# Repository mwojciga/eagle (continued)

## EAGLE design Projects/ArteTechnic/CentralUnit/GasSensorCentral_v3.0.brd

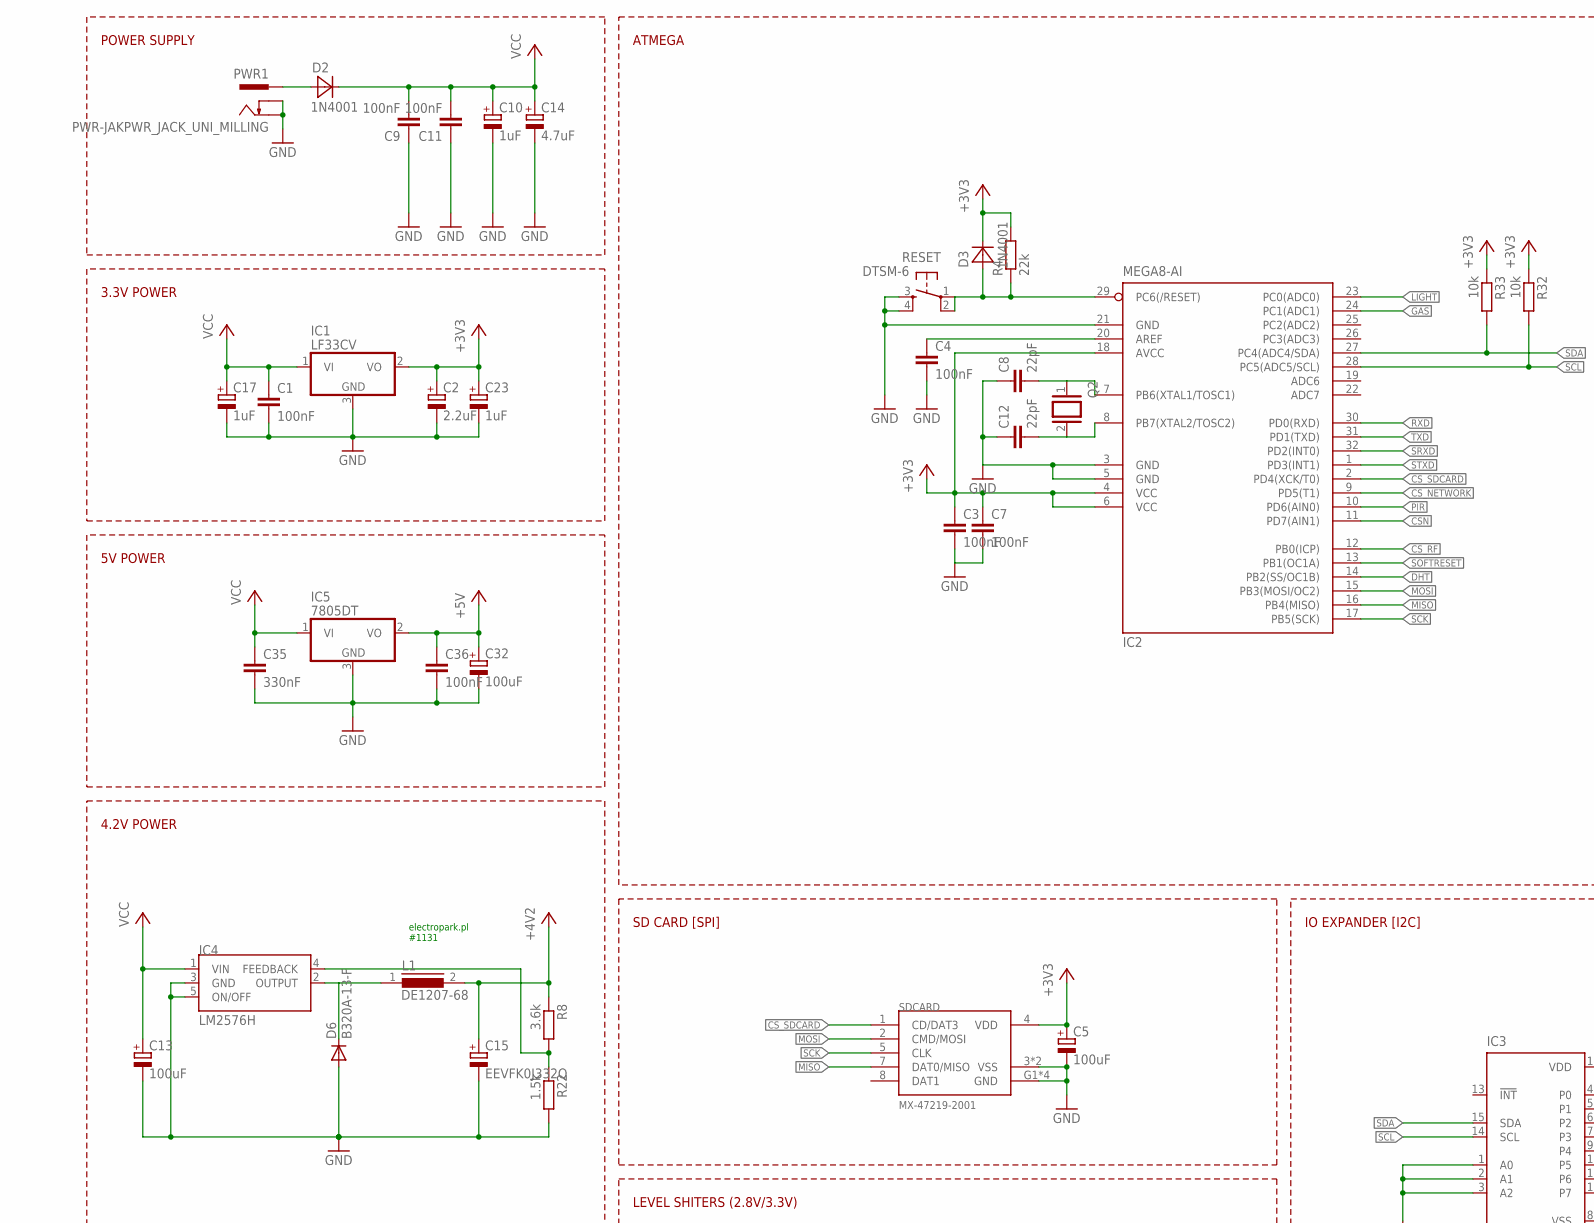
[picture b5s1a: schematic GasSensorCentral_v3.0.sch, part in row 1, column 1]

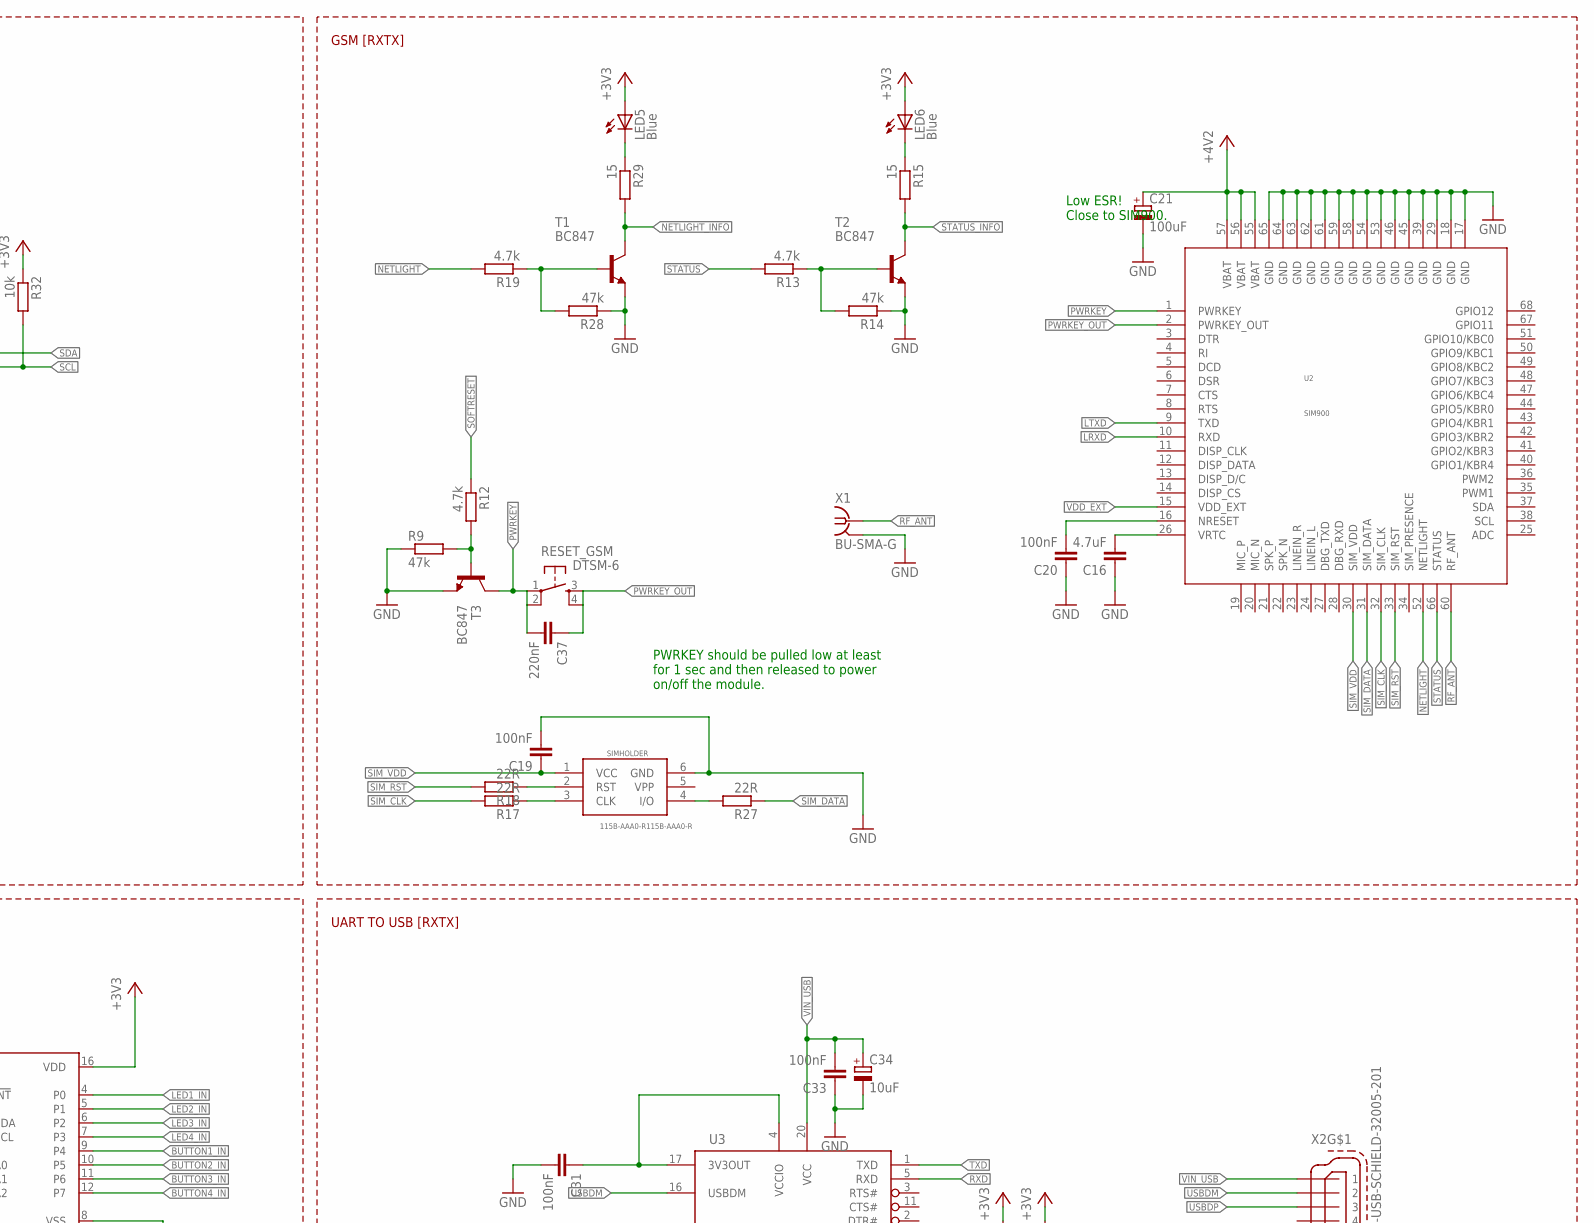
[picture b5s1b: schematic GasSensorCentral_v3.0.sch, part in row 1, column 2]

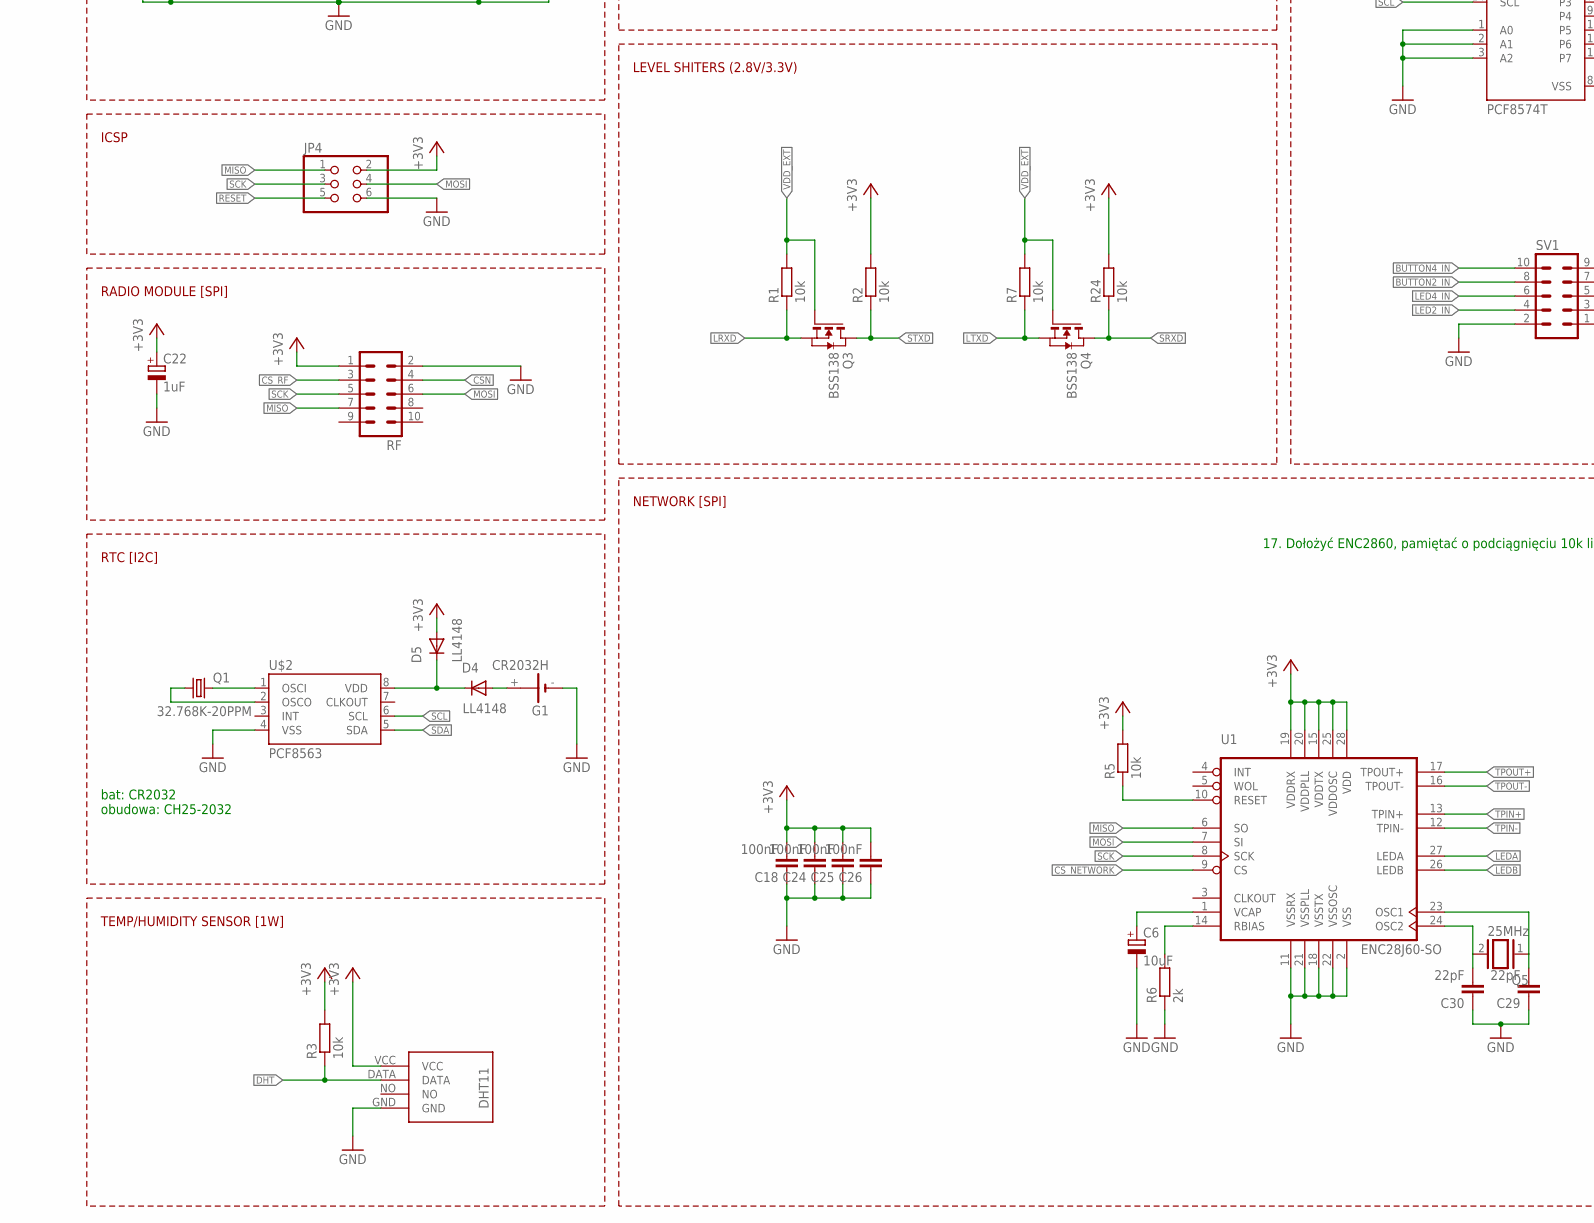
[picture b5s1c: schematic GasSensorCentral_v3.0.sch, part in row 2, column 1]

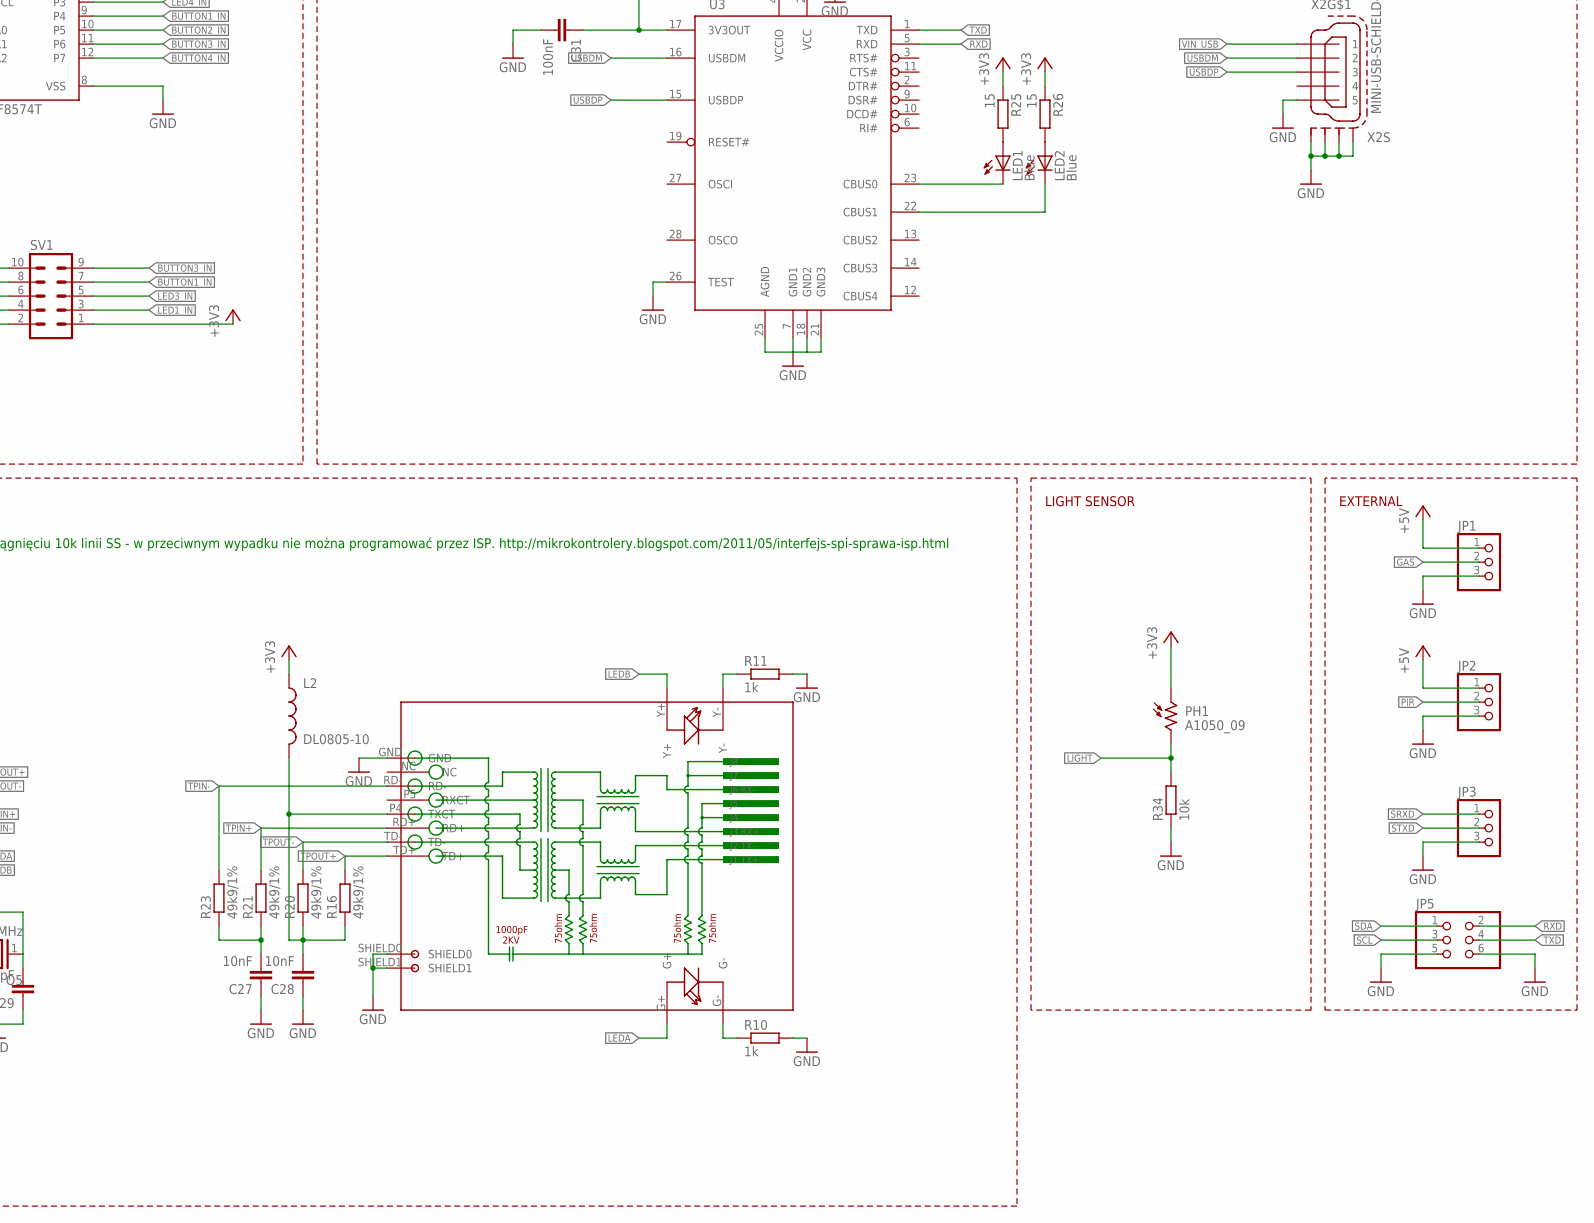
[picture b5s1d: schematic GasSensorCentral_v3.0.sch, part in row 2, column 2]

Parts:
C1, C3, C4, C7, C9, C11, C18, C19, C20, C24, C25, C26, C31, C33, C36: 100nF; C0805
C2: 2.2uF; PANASONIC_B
C5, C13, C21, C32: 100uF; PANASONIC_B
C6, C34: 10uF; PANASONIC_B
C8, C12, C29, C30: 22pF; C0805
C10, C17, C22, C23: 1uF; PANASONIC_B
C14: 4.7uF; PANASONIC_B
C15: EEVFK0J332Q; 153CLV-1212
C16: 4.7uF; C0805
C27, C28: 10nF; C0805
C35: 330nF; C0805
C37: 220nF; C0805
D2, D3: 1N4001; SMA
D4, D5: LL4148; SOD80C
D6: B320A-13-F; DO214AC
G1: CR2032H
IC1: LF33CV; TO252
IC2: MEGA8-AI; TQFP32-08
IC3: PCF8574T; SO16W
IC4: LM2576H; TO220-52
IC5: 7805DT; TO252
JP1, JP2, JP3: PINHD-1X3; 1X03
JP4, JP5: PINHD-2X3; 2X03
L1: DE1207-68; DE1207
L2: DL0805-10; 0805
LED1, LED2, LED5, LED6: Blue; SML0805
PH1: A1050_09; T0-46-A10XX
PWR1: PWR-JAKPWR_JACK_UNI_MILLING; PWR_JACK_UNI_MILLING
Q1: 32.768K-20PPM; TC26V
Q2: XTAL/S; QS
Q3, Q4: BSS138; SOT-23
Q5: 25MHz; QS
R1, R2, R3, R5, R7, R24, R32, R33, R34: 10k; R0805
R4: 22k; R0805
R6: 2k; R0805
R8: 3.6k; R0805
R9, R14, R28: 47k; R0805
R10, R11: 1k; R0805
R12, R13, R19: 4.7k; R0805
R15, R25, R26, R29: 15; R0805
R16, R20, R21, R23: 49k9/1%; R0805
R17, R18, R27: 22R; R0805
R22: 1.5k; R0805
RESET: DTSM-6
RESET_GSM: DTSM-6
RF: ML10
RJ1: HR911105A
SDCARD: MX-47219-2001
SIMHOLDER: 115B-AAA0-R115B-AAA0-R; 115B-AAA0-R
SV1: ML10
T1, T2, T3: BC847; SOT23
U1: ENC28J60-SO; SO28W
U2: SIM900
U3: FT232RL; SSOP28DB
U$2: PCF8563; SO08
U$3: DHT11-PION.
X1: BU-SMA-G
X2: MINI-USB-SCHIELD-32005-201; 32005-201

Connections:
+3V3: C2.+, C3.1, C5.+, C7.1, C18.2, C22.+, C23.+, C24.2, C25.2, C26.2, D3.C, D5.A, IC1.2 (VO), IC2.4 (VCC), IC2.6 (VCC), IC2.18 (AVCC), IC3.16 (VDD), JP4.2, L2.1, LED5.A, LED6.A, PH1.1, R2.2, R3.2, R4.2, R5.2, R24.2, R25.1, R26.1, R32.1, R33.1, RF.1, SDCARD.4 (VDD), SV1.1, U1.15 (VDDTX), U1.19 (VDDRX), U1.20 (VDDPLL), U1.25 (VDDOSC), U1.28 (VDD), U$3.VCC
+4V2: C15.+, C21.+, L1.2, R8.1, U2.55 (VBAT), U2.56 (VBAT), U2.57 (VBAT)
+5V: C32.+, C36.1, IC5.2 (VO), JP1.1, JP2.1
BUTTON1_IN: IC3.9 (P4), SV1.7
BUTTON2_IN: IC3.10 (P5), SV1.8
BUTTON3_IN: IC3.11 (P6), SV1.9
BUTTON4_IN: IC3.12 (P7), SV1.10
CSN: IC2.11 (PD7(AIN1)), RF.4
CS_NETWORK: IC2.9 (PD5(T1)), U1.9 (CS)
CS_RF: IC2.12 (PB0(ICP)), RF.3
CS_SDCARD: IC2.2 (PD4(XCK/T0)), SDCARD.1 (CD/DAT3)
DHT: IC2.14 (PB2(SS/OC1B)), R3.1, U$3.DATA
GAS: IC2.24 (PC1(ADC1)), JP1.2
GND: C1.2, C2.-, C3.2, C4.2, C5.-, C6.-, C7.2, C8.1, C9.1, C10.-, C11.1, C12.1, C13.-, C14.-, C15.-, C16.1, C17.-, C18.1, C19.2, C20.1, C21.-, C22.-, C23.-, C24.1, C25.1, C26.1, C27.1, C28.1, C29.1, C30.1, C31.2, C32.-, C33.1, C34.-, C35.2, C36.2, G1.-, IC1.3 (GND), IC2.3 (GND), IC2.5 (GND), IC2.21 (GND), IC3.1 (A0), IC3.2 (A1), IC3.3 (A2), IC3.8 (VSS), IC4.3 (GND), IC4.5 (ON/OFF), IC5.3 (GND), JP1.3, JP2.3, JP3.3, JP4.6, JP5.5, JP5.6, PWR1.-, PWR1.-1 (-), PWR1.-2 (-), PWR1.-3 (-), PWR1.-4 (-), PWR1.-5 (-), PWR1.-6 (-), PWR1.--, PWR1.--1 (--), PWR1.--2 (--), PWR1.--3 (--), PWR1.--4 (--), PWR1.--5 (--), PWR1.--6 (--), R6.1, R9.1, R10.2, R11.2, R14.1, R22.2, R28.1, R34.1, RESET.3, RESET.4, RF.2, RJ1.GND, RJ1.SHIELD0, RJ1.SHIELD1, SDCARD.3 (VSS), SDCARD.6 (VSS), SDCARD.G1 (GND), SDCARD.G2 (GND), SDCARD.G3 (GND), SDCARD.G4 (GND), SIMHOLDER.6 (GND), SV1.2, T1.2 (E), T2.2 (E), T3.2 (E), U1.2 (VSS), U1.11 (VSSRX), U1.18 (VSSTX), U1.21 (VSSPLL), U1.22 (VSSOSC), U2.17 (GND), U2.18 (GND), U2.29 (GND), U2.39 (GND), U2.45 (GND), U2.46 (GND), U2.53 (GND), U2.54 (GND), U2.58 (GND), U2.59 (GND), U2.61 (GND), U2.62 (GND), U2.63 (GND), U2.64 (GND), U2.65 (GND), U3.7 (GND1), U3.18 (GND2), U3.21 (GND3), U3.25 (AGND), U3.26 (TEST), U$2.4 (VSS), U$3.GND, X1.2, X1.3 (2), X1.4 (2), X1.5 (2), X2.5, X2.M1 (S1), X2.M2 (S2), X2.M3 (S3), X2.M4 (S4)
LED1_IN: IC3.4 (P0), SV1.3
LED2_IN: IC3.5 (P1), SV1.4
LED3_IN: IC3.6 (P2), SV1.5
LED4_IN: IC3.7 (P3), SV1.6
LEDA: RJ1.G+, U1.27 (LEDA)
LEDB: RJ1.Y+, U1.26 (LEDB)
LIGHT: IC2.23 (PC0(ADC0)), PH1.2, R34.2
LRXD: Q3.2 (S), R1.1, U2.10 (RXD)
LTXD: Q4.2 (S), R7.1, U2.9 (TXD)
MISO: IC2.16 (PB4(MISO)), JP4.1, RF.7, SDCARD.7 (DAT0/MISO), U1.6 (SO)
MOSI: IC2.15 (PB3(MOSI/OC2)), JP4.4, RF.6, SDCARD.2 (CMD/MOSI), U1.7 (SI)
unnamed: C4.1, IC2.20 (AREF)
unnamed: Q1.1, U$2.2 (OSCO)
unnamed: IC4.4 (FEEDBACK), R8.2, R22.1
unnamed: D2.A, PWR1.+, PWR1.+1 (+), PWR1.+2 (+), PWR1.+3 (+), PWR1.+4 (+), PWR1.+5 (+), PWR1.+6 (+)
unnamed: D4.C, D5.C, U$2.8 (VDD)
unnamed: R27.2, SIMHOLDER.4 (I/O)
unnamed: LED5.C, R29.1
unnamed: Q1.2, U$2.1 (OSCI)
unnamed: R13.1, R14.2, T2.1 (B)
unnamed: LED6.C, R15.1
unnamed: D6.C, IC4.2 (OUTPUT), L1.1
unnamed: C20.2, U2.16 (NRESET)
unnamed: R9.2, R12.2, T3.1 (B)
unnamed: R19.1, R28.2, T1.1 (B)
unnamed: D4.A, G1.+
unnamed: C16.2, U2.26 (VRTC)
unnamed: R5.1, U1.10 (RESET)
unnamed: C6.+, U1.1 (VCAP)
unnamed: R6.2, U1.14 (RBIAS)
unnamed: R11.1, RJ1.Y-
unnamed: R10.1, RJ1.G-
unnamed: C29.2, Q5.1, U1.23 (OSC1)
unnamed: R18.1, SIMHOLDER.2 (RST)
unnamed: R17.1, SIMHOLDER.3 (CLK)
unnamed: C30.2, Q5.2, U1.24 (OSC2)
unnamed: LED1.C, U3.23 (CBUS0)
unnamed: LED2.C, U3.22 (CBUS1)
unnamed: C8.2, IC2.7 (PB6(XTAL1/TOSC1)), Q2.1
unnamed: C27.2, R21.1, R23.1
unnamed: C28.2, L2.2, R16.1, R20.1, RJ1.P4 (TXCT)
unnamed: LED1.A, R25.2
unnamed: LED2.A, R26.2
unnamed: C12.2, IC2.8 (PB7(XTAL2/TOSC2)), Q2.2
unnamed: C31.1, U3.4 (VCCIO), U3.17 (3V3OUT)
NETLIGHT: R19.2, U2.52 (NETLIGHT)
NETLIGHT_INFO: R29.2, T1.3 (C)
PIR: IC2.10 (PD6(AIN0)), JP2.2
PWRKEY: C37.2, RESET_GSM.1, RESET_GSM.2, T3.3 (C), U2.1 (PWRKEY)
PWRKEY_OUT: C37.1, RESET_GSM.3, RESET_GSM.4, U2.2 (PWRKEY_OUT)
RESET: D3.A, IC2.29 (PC6(/RESET)), JP4.5, R4.1, RESET.1, RESET.2
RF_ANT: U2.60 (RF_ANT), X1.1
RXD: IC2.30 (PD0(RXD)), JP5.2, U3.5 (RXD)
SCK: IC2.17 (PB5(SCK)), JP4.3, RF.5, SDCARD.5 (CLK), U1.8 (SCK)
SCL: IC2.28 (PC5(ADC5/SCL)), IC3.14 (SCL), JP5.3, R32.2, U$2.6 (SCL)
SDA: IC2.27 (PC4(ADC4/SDA)), IC3.15 (SDA), JP5.1, R33.2, U$2.5 (SDA)
SIM_CLK: R17.2, U2.32 (SIM_CLK)
SIM_DATA: R27.1, U2.31 (SIM_DATA)
SIM_RST: R18.2, U2.33 (SIM_RST)
SIM_VDD: C19.1, SIMHOLDER.1 (VCC), U2.30 (SIM_VDD)
SOFTRESET: IC2.13 (PB1(OC1A)), R12.1
SRXD: IC2.32 (PD2(INT0)), JP3.1, Q4.1 (D), R24.1
STATUS: R13.2, U2.66 (STATUS)
STATUS_INFO: R15.2, T2.3 (C)
STXD: IC2.1 (PD3(INT1)), JP3.2, Q3.1 (D), R2.1
TPIN+: R21.2, RJ1.RD+, U1.13 (TPIN+)
TPIN-: R23.2, RJ1.RD-, U1.12 (TPIN-)
TPOUT+: R16.2, RJ1.TD+, U1.17 (TPOUT+)
TPOUT-: R20.2, RJ1.TD-, U1.16 (TPOUT-)
TXD: IC2.31 (PD1(TXD)), JP5.4, U3.1 (TXD)
USBDM: U3.16 (USBDM), X2.2
USBDP: U3.15 (USBDP), X2.3
VCC: C1.1, C9.2, C10.+, C11.2, C13.+, C14.+, C17.+, C35.1, D2.C, IC1.1 (VI), IC4.1 (VIN), IC5.1 (VI)
VDD_EXT: Q3.3 (G), Q4.3 (G), R1.2, R7.2, U2.15 (VDD_EXT)
VIN_USB: C33.2, C34.+, U3.20 (VCC), X2.1

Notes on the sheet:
PWRKEY should be pulled low at least for 1 sec and then released to power on/off the module.
Low ESR! Close to SIM900.
bat: CR2032 obudowa: CH25-2032
POWER SUPPLY
3.3V POWER
ICSP
4.2V POWER
RADIO MODULE [SPI]
LEVEL SHITERS (2.8V/3.3V)
ATMEGA
SD CARD [SPI]
RTC [I2C]
GSM [RXTX]
NETWORK [SPI]
17. Dołożyć ENC2860, pamiętać o podciągnięciu 10k linii SS - w przeciwnym wypadku nie można programować przez ISP. http://mikrokontrolery.blogspot.com/2011/05/interfejs-spi-sprawa-isp.html
IO EXPANDER [I2C]
TEMP/HUMIDITY SENSOR [1W]
electropark.pl #1131
UART TO USB [RXTX]
LIGHT SENSOR
EXTERNAL
5V POWER

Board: 2 copper layers, 115 parts (5 on the bottom side), 89 nets, no tracks yet.

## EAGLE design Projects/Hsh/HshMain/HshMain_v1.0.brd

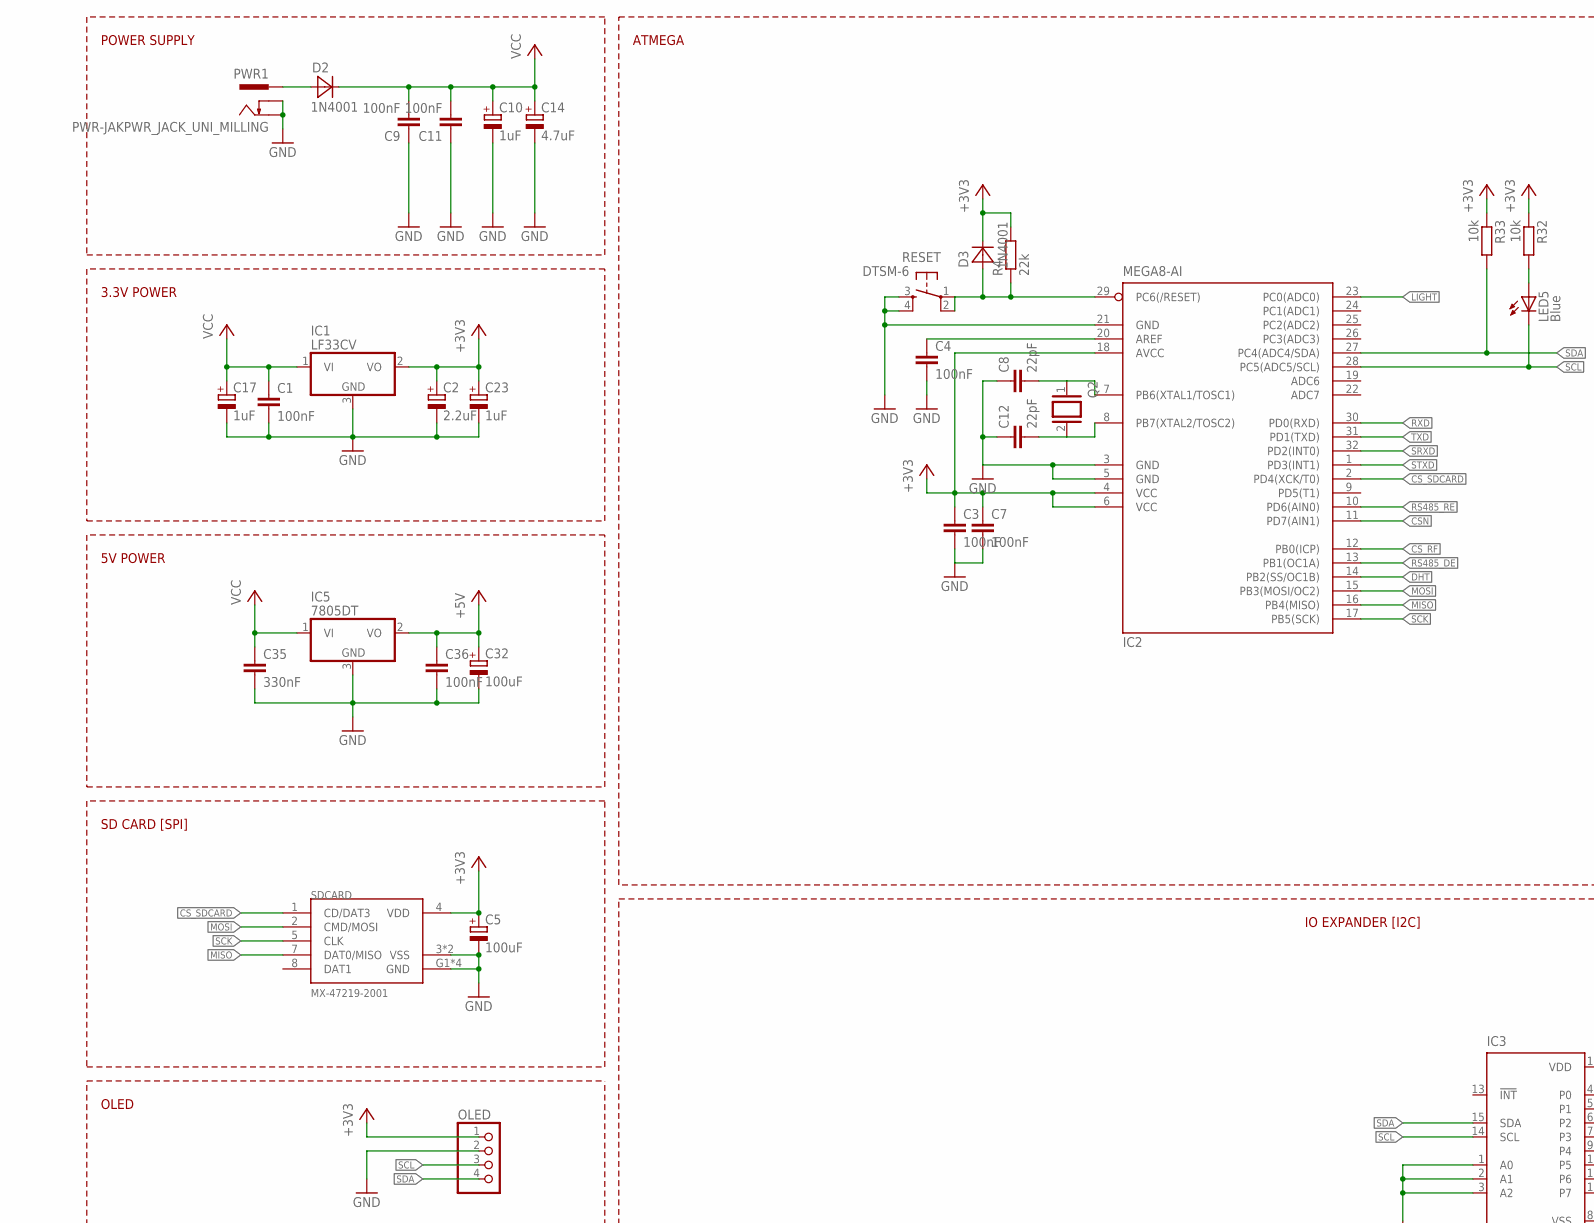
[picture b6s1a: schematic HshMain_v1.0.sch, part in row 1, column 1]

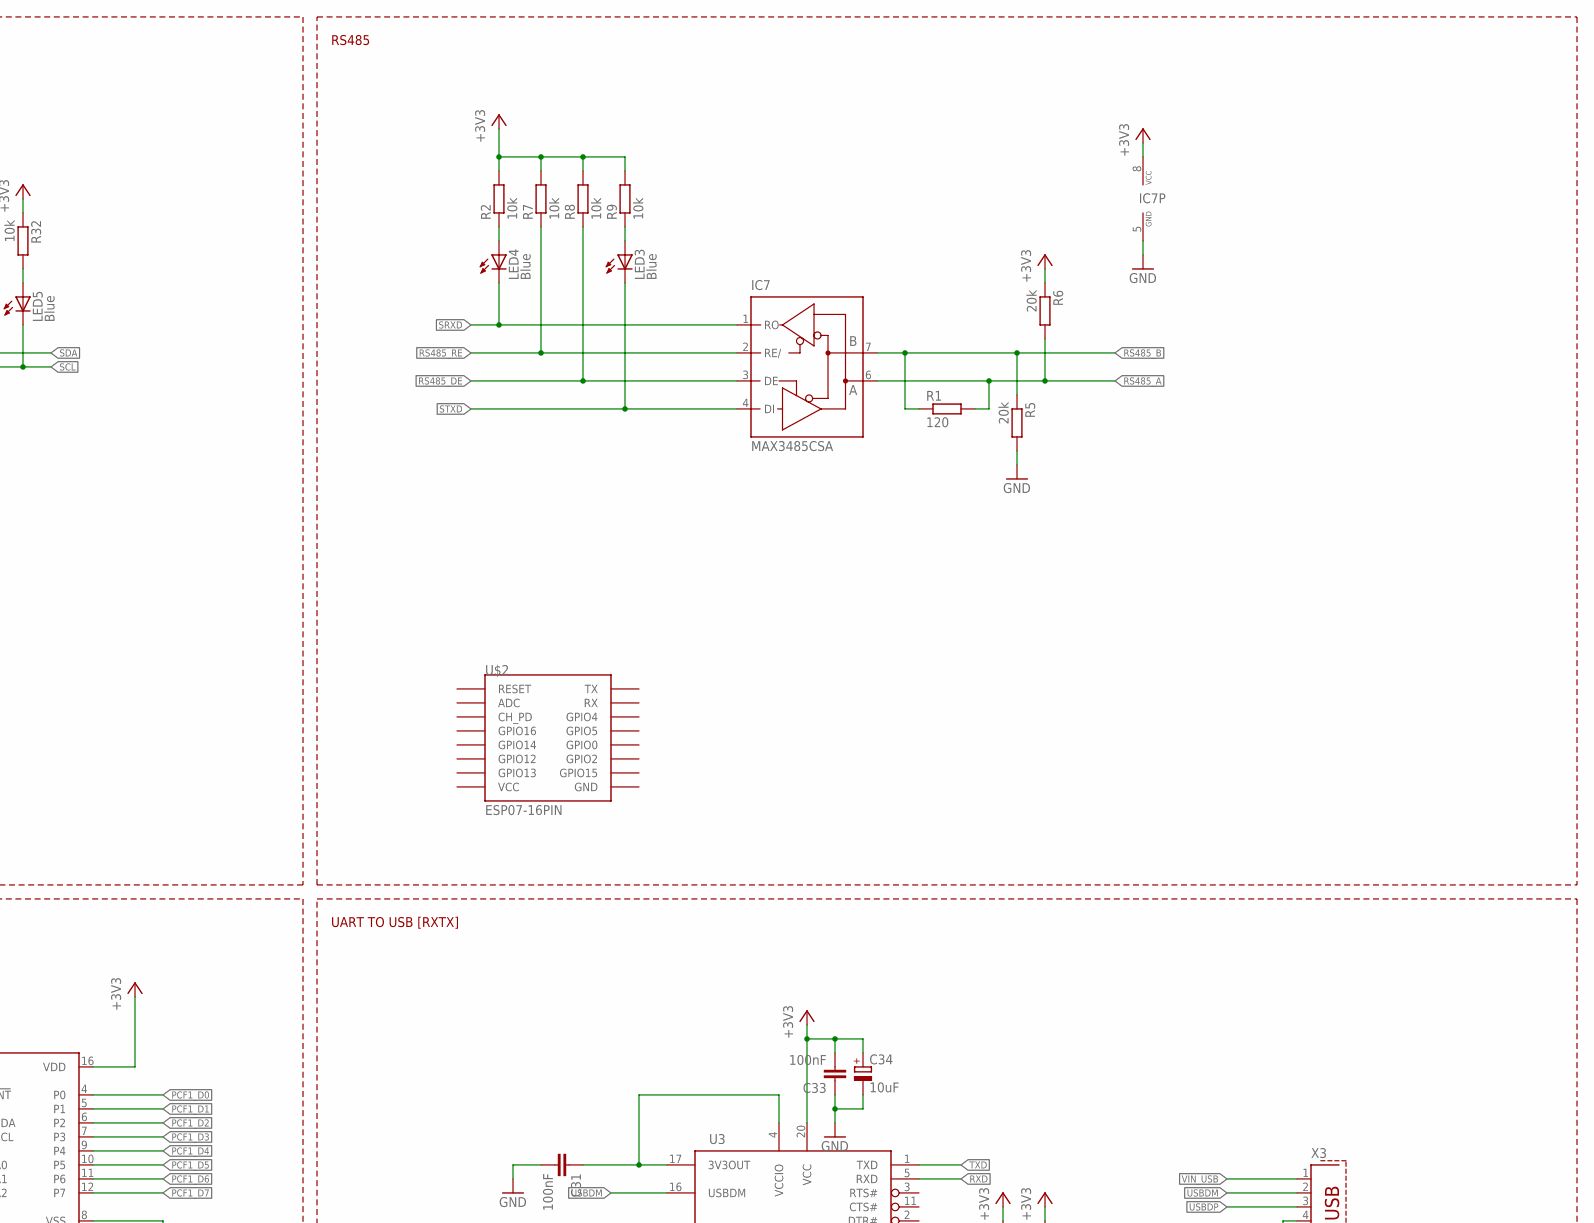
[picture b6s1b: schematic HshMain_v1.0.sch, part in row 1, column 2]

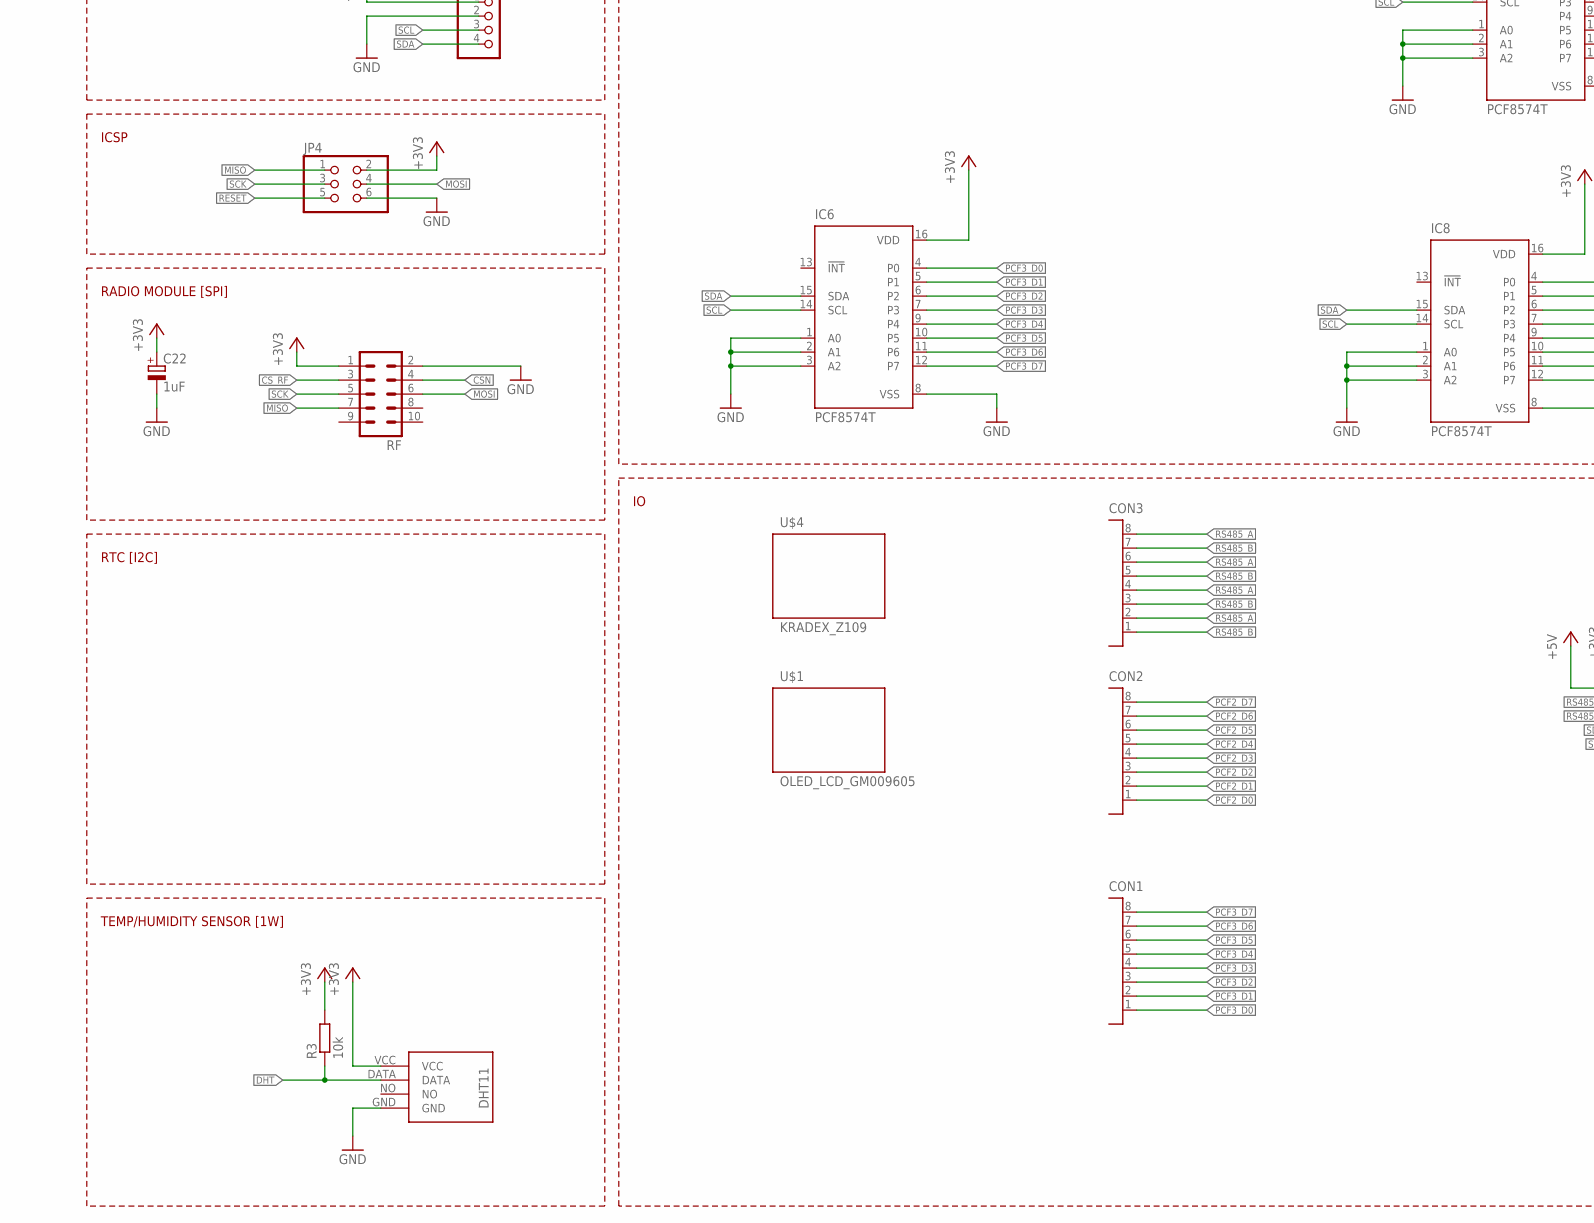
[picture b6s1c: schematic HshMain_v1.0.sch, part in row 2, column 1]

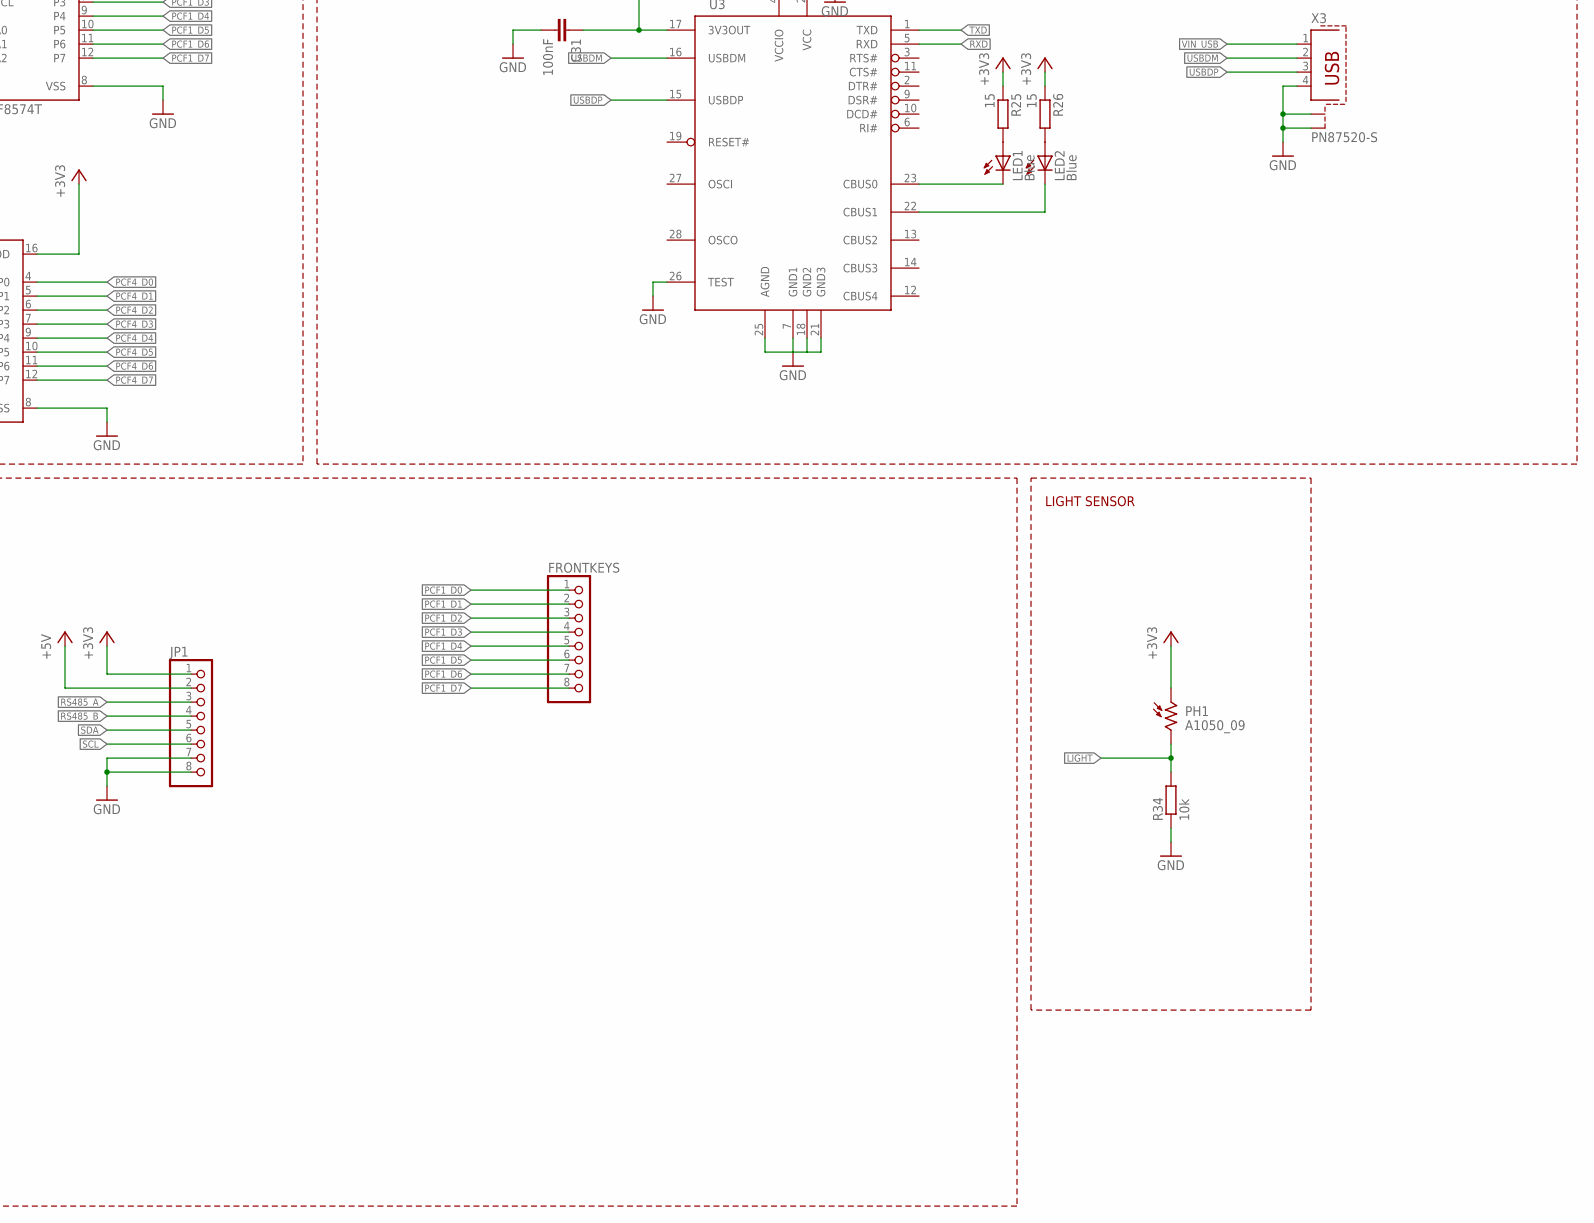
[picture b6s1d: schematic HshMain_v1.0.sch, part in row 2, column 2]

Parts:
C1, C3, C4, C7, C9, C11, C31, C33, C36: 100nF; C0805
C2: 2.2uF; PANASONIC_B
C5, C32: 100uF; PANASONIC_D
C8, C12: 22pF; C0805
C10, C17, C22, C23: 1uF; PANASONIC_B
C14: 4.7uF; PANASONIC_B
C34: 10uF; PANASONIC_B
C35: 330nF; C0805
CON1, CON2, CON3: 15EDGRC-3.81-8P
D2, D3: 1N4001; SMA
FRONTKEYS: PINHD-1X8/90; 1X08/90
IC1: LF33CV; TO252
IC2: MEGA8-AI; TQFP32-08
IC3, IC6, IC8: PCF8574T; SO16W
IC5: 7805DT; TO252
IC7: MAX3485CSA; SO08
JP1: PINHD-1X8/90; 1X08/90
JP4: PINHD-2X3; 2X03
LED1, LED2, LED3, LED4, LED5: Blue; SML0805
OLED: PINHD-1X4; 1X04
PH1: A1050_09; T0-46-A10XX
PWR1: PWR-JAKPWR_JACK_UNI_MILLING; PWR_JACK_UNI_MILLING
Q2: XTAL/S; QS
R1: 120; R0805
R2, R3, R7, R8, R9, R32, R33, R34: 10k; R0805
R4: 22k; R0805
R5, R6: 20k; R0805
R25, R26: 15; R0805
RESET: DTSM-6
RF: ML10
SDCARD: MX-47219-2001
U3: FT232RL; SSOP28DB
U$1: OLED_LCD_GM009605
U$2: ESP07-16PIN
U$3: DHT11-PION.
U$4: KRADEX_Z109
X3: PN87520-S

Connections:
+3V3: C2.+, C3.1, C5.+, C7.1, C22.+, C23.+, C33.2, C34.+, D3.C, IC1.2 (VO), IC2.4 (VCC), IC2.6 (VCC), IC2.18 (AVCC), IC3.16 (VDD), IC6.16 (VDD), IC7.8 (VCC), IC8.16 (VDD), JP1.1, JP4.2, OLED.1, PH1.1, R2.2, R3.2, R4.2, R6.1, R7.2, R8.2, R9.2, R25.1, R26.1, R32.1, R33.1, RF.1, SDCARD.4 (VDD), U3.20 (VCC), U$3.VCC
+5V: C32.+, C36.1, IC5.2 (VO), JP1.2
CSN: IC2.11 (PD7(AIN1)), RF.4
CS_RF: IC2.12 (PB0(ICP)), RF.3
CS_SDCARD: IC2.2 (PD4(XCK/T0)), SDCARD.1 (CD/DAT3)
DHT: IC2.14 (PB2(SS/OC1B)), R3.1, U$3.DATA
GND: C1.2, C2.-, C3.2, C4.2, C5.-, C7.2, C8.1, C9.1, C10.-, C11.1, C12.1, C14.-, C17.-, C22.-, C23.-, C31.2, C32.-, C33.1, C34.-, C35.2, C36.2, IC1.3 (GND), IC2.3 (GND), IC2.5 (GND), IC2.21 (GND), IC3.1 (A0), IC3.2 (A1), IC3.3 (A2), IC3.8 (VSS), IC5.3 (GND), IC6.1 (A0), IC6.2 (A1), IC6.3 (A2), IC6.8 (VSS), IC7.5 (GND), IC8.1 (A0), IC8.2 (A1), IC8.3 (A2), IC8.8 (VSS), JP1.7, JP1.8, JP4.6, OLED.2, PWR1.-, PWR1.-1 (-), PWR1.-2 (-), PWR1.-3 (-), PWR1.-4 (-), PWR1.-5 (-), PWR1.-6 (-), PWR1.-7 (-), PWR1.-8 (-), PWR1.--, PWR1.--1 (--), PWR1.--2 (--), PWR1.--3 (--), PWR1.--4 (--), PWR1.--5 (--), PWR1.--6 (--), PWR1.--7 (--), PWR1.--8 (--), R5.2, R34.1, RESET.3, RESET.4, RF.2, SDCARD.3 (VSS), SDCARD.6 (VSS), SDCARD.G1 (GND), SDCARD.G2 (GND), SDCARD.G3 (GND), SDCARD.G4 (GND), U3.7 (GND1), U3.18 (GND2), U3.21 (GND3), U3.25 (AGND), U3.26 (TEST), U$3.GND, X3.4, X3.S1, X3.S2
LIGHT: IC2.23 (PC0(ADC0)), PH1.2, R34.2
MISO: IC2.16 (PB4(MISO)), JP4.1, RF.7, SDCARD.7 (DAT0/MISO)
MOSI: IC2.15 (PB3(MOSI/OC2)), JP4.4, RF.6, SDCARD.2 (CMD/MOSI)
unnamed: C4.1, IC2.20 (AREF)
unnamed: LED4.A, R2.1
unnamed: LED3.A, R9.1
unnamed: D2.A, PWR1.+, PWR1.+1 (+), PWR1.+2 (+), PWR1.+3 (+), PWR1.+4 (+), PWR1.+5 (+), PWR1.+6 (+), PWR1.+7 (+), PWR1.+8 (+)
unnamed: LED5.A, R32.2
unnamed: LED1.C, U3.23 (CBUS0)
unnamed: LED2.C, U3.22 (CBUS1)
unnamed: C8.2, IC2.7 (PB6(XTAL1/TOSC1)), Q2.1
unnamed: LED1.A, R25.2
unnamed: LED2.A, R26.2
unnamed: C12.2, IC2.8 (PB7(XTAL2/TOSC2)), Q2.2
unnamed: C31.1, U3.4 (VCCIO), U3.17 (3V3OUT)
PCF1_D0: FRONTKEYS.1, IC3.4 (P0)
PCF1_D1: FRONTKEYS.2, IC3.5 (P1)
PCF1_D2: FRONTKEYS.3, IC3.6 (P2)
PCF1_D3: FRONTKEYS.4, IC3.7 (P3)
PCF1_D4: FRONTKEYS.5, IC3.9 (P4)
PCF1_D5: FRONTKEYS.6, IC3.10 (P5)
PCF1_D6: FRONTKEYS.7, IC3.11 (P6)
PCF1_D7: FRONTKEYS.8, IC3.12 (P7)
PCF2_D0: CON2.1
PCF2_D1: CON2.2
PCF2_D2: CON2.3
PCF2_D3: CON2.4
PCF2_D4: CON2.5
PCF2_D5: CON2.6
PCF2_D6: CON2.7
PCF2_D7: CON2.8
PCF3_D0: CON1.1, IC6.4 (P0)
PCF3_D1: CON1.2, IC6.5 (P1)
PCF3_D2: CON1.3, IC6.6 (P2)
PCF3_D3: CON1.4, IC6.7 (P3)
PCF3_D4: CON1.5, IC6.9 (P4)
PCF3_D5: CON1.6, IC6.10 (P5)
PCF3_D6: CON1.7, IC6.11 (P6)
PCF3_D7: CON1.8, IC6.12 (P7)
PCF4_D0: IC8.4 (P0)
PCF4_D1: IC8.5 (P1)
PCF4_D2: IC8.6 (P2)
PCF4_D3: IC8.7 (P3)
PCF4_D4: IC8.9 (P4)
PCF4_D5: IC8.10 (P5)
PCF4_D6: IC8.11 (P6)
PCF4_D7: IC8.12 (P7)
RESET: D3.A, IC2.29 (PC6(/RESET)), JP4.5, R4.1, RESET.1, RESET.2
RS485_A: CON3.2, CON3.4, CON3.6, CON3.8, IC7.6 (A), JP1.3, R1.2, R6.2
RS485_B: CON3.1, CON3.3, CON3.5, CON3.7, IC7.7 (B), JP1.4, R1.1, R5.1
RS485_DE: IC2.13 (PB1(OC1A)), IC7.3 (DE), R8.1
RS485_RE: IC2.10 (PD6(AIN0)), IC7.2 (RE/), R7.1
RXD: IC2.30 (PD0(RXD)), U3.5 (RXD)
SCK: IC2.17 (PB5(SCK)), JP4.3, RF.5, SDCARD.5 (CLK)
SCL: IC2.28 (PC5(ADC5/SCL)), IC3.14 (SCL), IC6.14 (SCL), IC8.14 (SCL), JP1.6, LED5.C, OLED.3
SDA: IC2.27 (PC4(ADC4/SDA)), IC3.15 (SDA), IC6.15 (SDA), IC8.15 (SDA), JP1.5, OLED.4, R33.2
SRXD: IC2.32 (PD2(INT0)), IC7.1 (RO), LED4.C
STXD: IC2.1 (PD3(INT1)), IC7.4 (DI), LED3.C
TXD: IC2.31 (PD1(TXD)), U3.1 (TXD)
USBDM: U3.16 (USBDM), X3.2
USBDP: U3.15 (USBDP), X3.3
VCC: C1.1, C9.2, C10.+, C11.2, C14.+, C17.+, C35.1, D2.C, IC1.1 (VI), IC5.1 (VI)
VIN_USB: X3.1

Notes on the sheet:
POWER SUPPLY
3.3V POWER
ICSP
RADIO MODULE [SPI]
ATMEGA
SD CARD [SPI]
RTC [I2C]
IO EXPANDER [I2C]
TEMP/HUMIDITY SENSOR [1W]
UART TO USB [RXTX]
LIGHT SENSOR
5V POWER
RS485
OLED

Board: 2 copper layers, 68 parts (4 on the bottom side), 53 nets, no tracks yet.
